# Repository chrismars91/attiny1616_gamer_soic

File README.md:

https://www.instructables.com/RGB-LED-Pocket-Gamer/
<br>
The image below and the KiCad files in this repo are for an ATtiny1616 SOIC. The instructables show an ATtiny1616 QFN.

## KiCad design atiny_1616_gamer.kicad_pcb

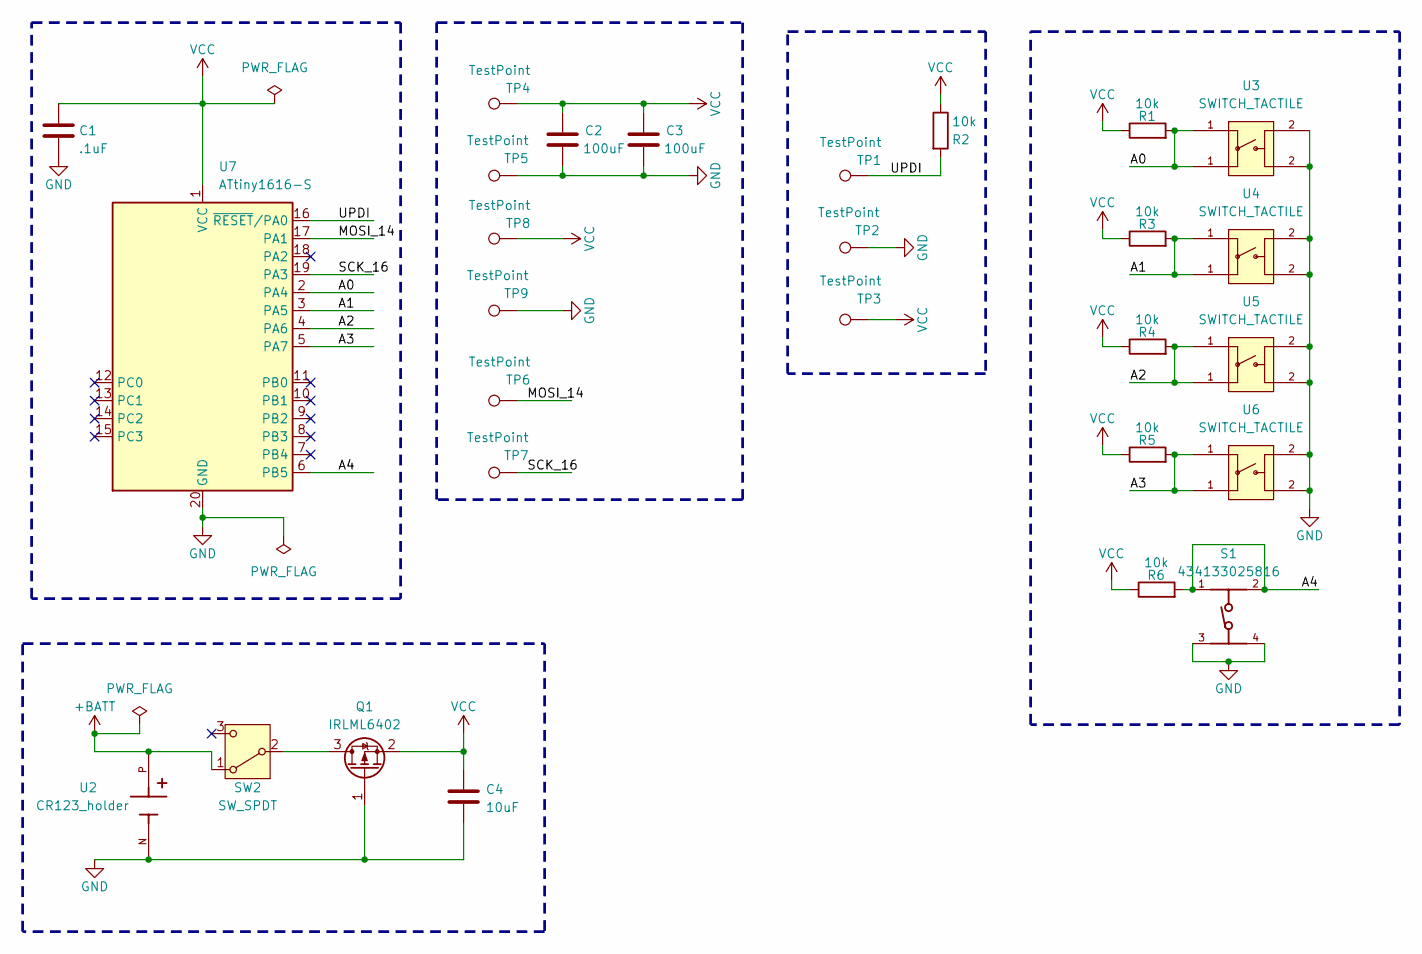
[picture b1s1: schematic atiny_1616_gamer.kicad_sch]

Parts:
C1: .1uF; C_0603_1608Metric
C2, C3: 100uF; C_1206_3216Metric
C4: 10uF; C_0603_1608Metric
Q1: IRLML6402; SOT-23
R1, R2, R3, R4, R5, R6: 10k; R_0603_1608Metric
S1: 434133025816
SW2: SW_SPDT; slide_switch_450404015514
TP1, TP2, TP3: TestPoint; TestPoint_Pad_2.0x2.0mm
TP4, TP5, TP6, TP7, TP8, TP9: TestPoint; TestPoint_Pad_1.5x1.5mm
U2: CR123_holder
U3, U4, U5, U6: SWITCH_TACTILE
U7: ATtiny1616-S; SOIC-20W_7.5x12.8mm_P1.27mm

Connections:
+BATT: SW2.1 (A), U2.P
/A0: R1.2, U3.1, U7.2 (PA4)
/A1: R3.2, U4.1, U7.3 (PA5)
/A2: R4.2, U5.1, U7.4 (PA6)
/A3: R5.2, U6.1, U7.5 (PA7)
/A4: R6.2, S1.1, S1.2, U7.6 (PB5)
/MOSI_14: TP6.1, U7.17 (PA1)
/SCK_16: TP7.1, U7.19 (PA3)
/UPDI: R2.2, TP1.1, U7.16 (~RESET/PA0)
GND: C1.2, C2.2, C3.2, C4.2, Q1.1 (G), S1.3, S1.4, TP2.1, TP5.1, TP9.1, U2.N, U3.2, U4.2, U5.2, U6.2, U7.20 (GND)
unnamed: Q1.3 (D), SW2.2 (B)
VCC: C1.1, C2.1, C3.1, C4.1, Q1.2 (S), R1.1, R2.1, R3.1, R4.1, R5.1, R6.1, TP3.1, TP4.1, TP8.1, U7.1 (VCC)

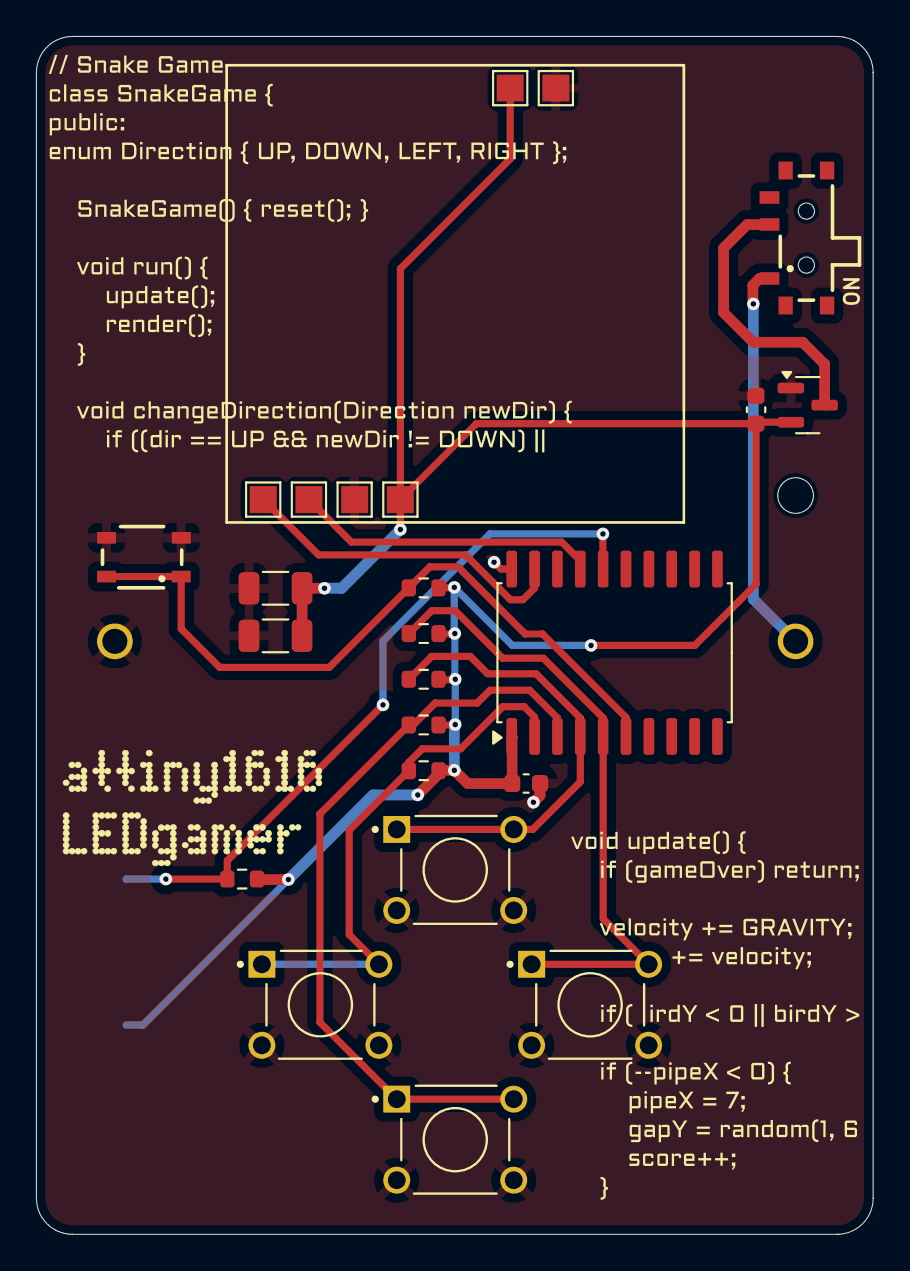
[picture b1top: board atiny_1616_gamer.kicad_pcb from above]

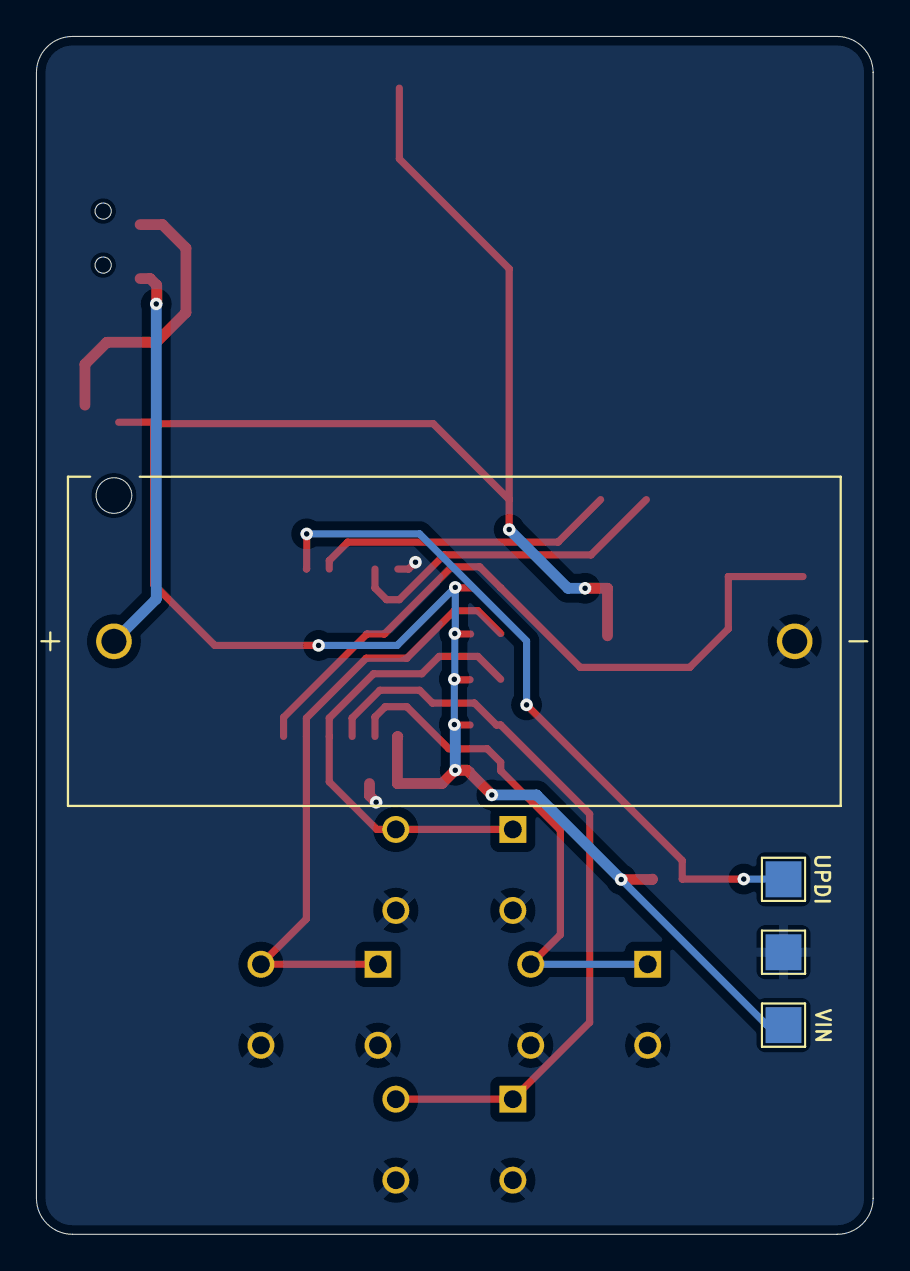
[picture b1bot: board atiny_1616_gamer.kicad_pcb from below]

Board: 2 copper layers, 46.5 x 66.5 mm, 28 parts (4 on the bottom side), 12 nets.

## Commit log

2025-04-14 init
